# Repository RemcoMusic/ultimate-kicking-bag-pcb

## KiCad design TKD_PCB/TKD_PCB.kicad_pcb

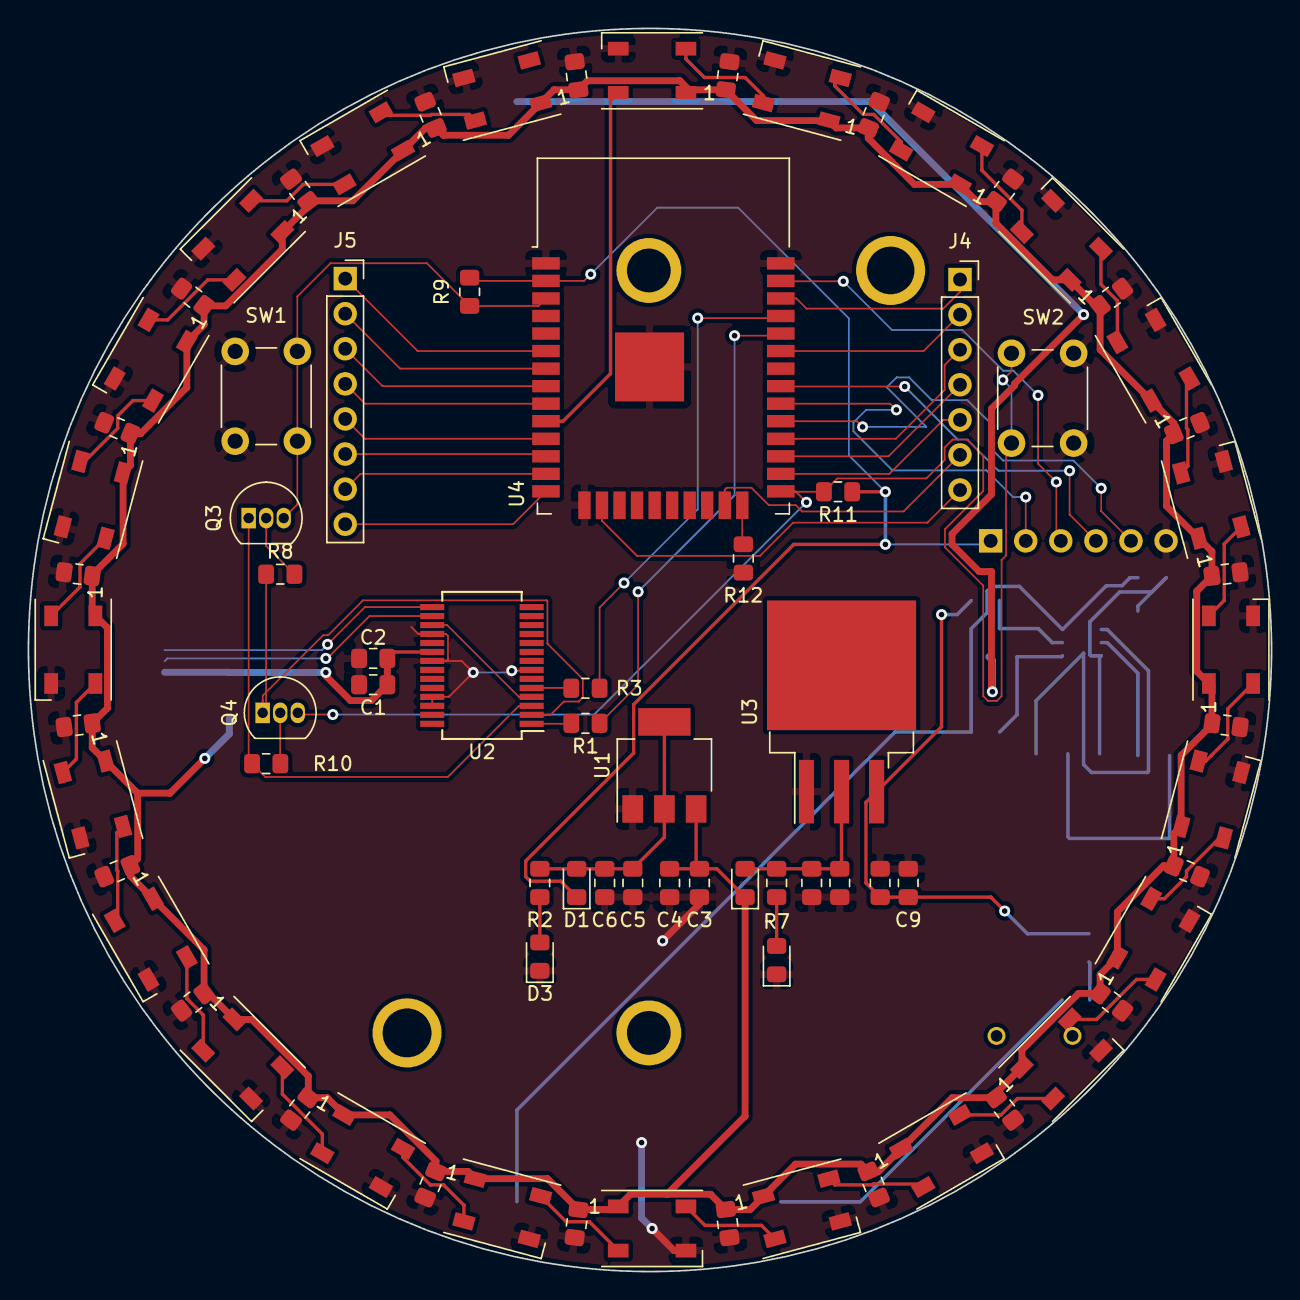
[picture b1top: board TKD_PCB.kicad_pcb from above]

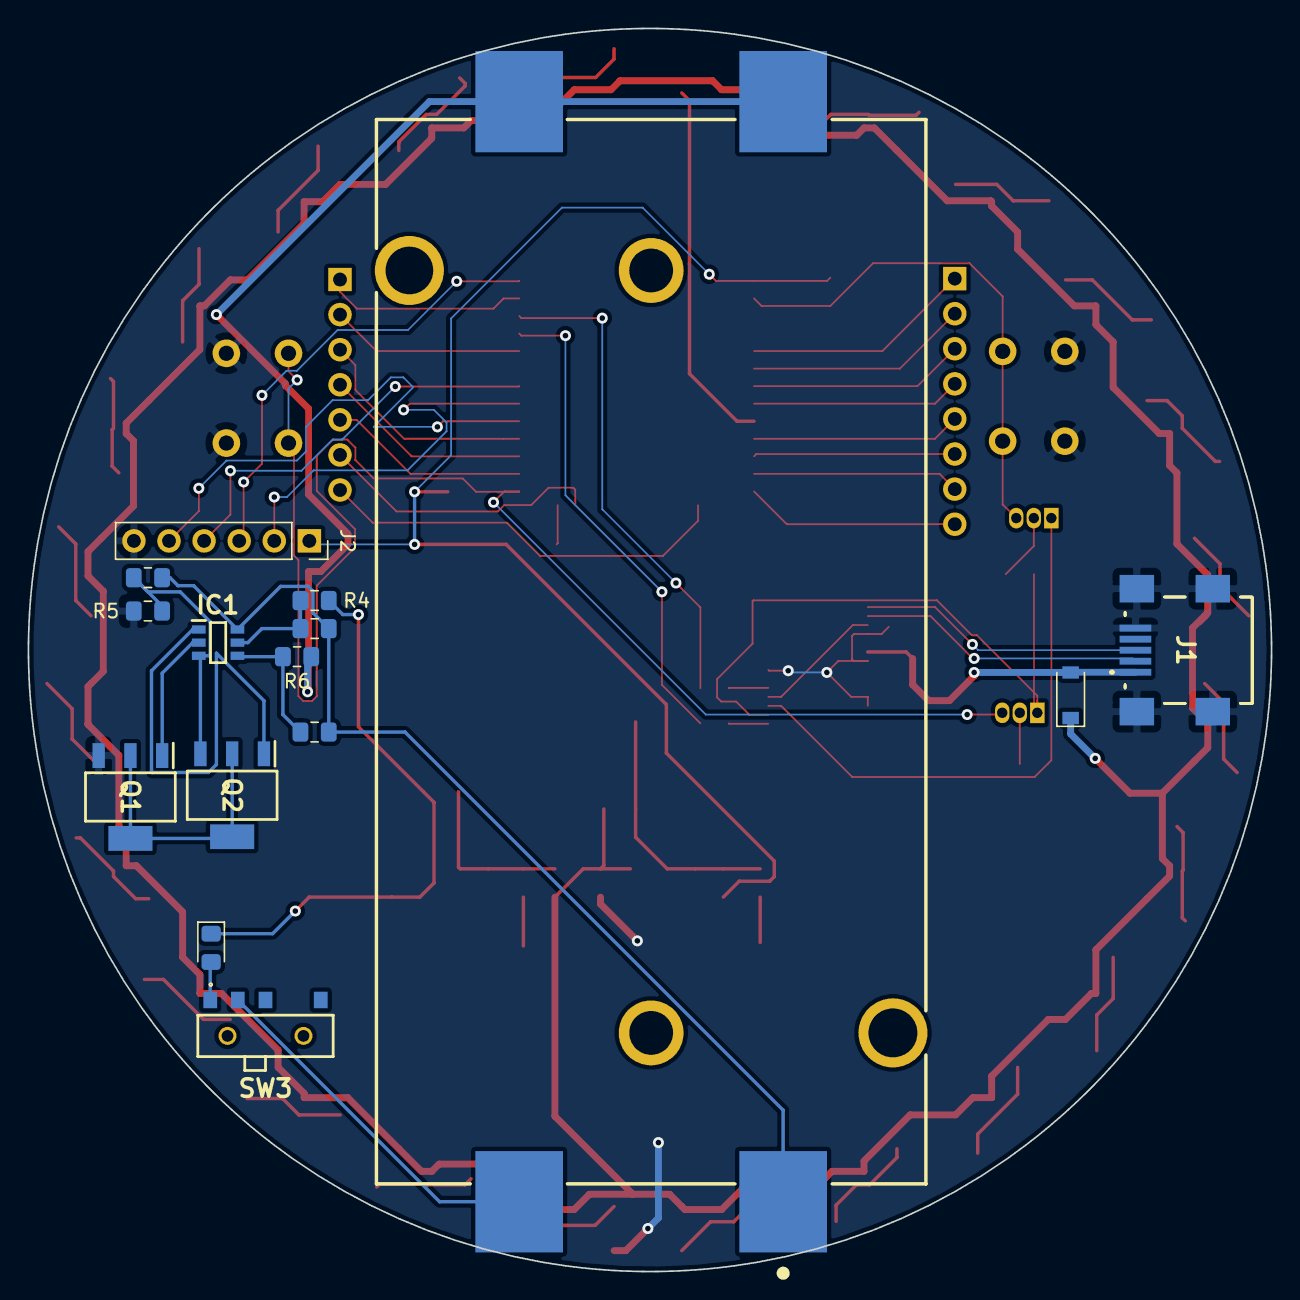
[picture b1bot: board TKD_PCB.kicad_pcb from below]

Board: 2 copper layers, 90.0 x 90.0 mm, 96 parts (15 on the bottom side), 76 nets.

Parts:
C1, C4, C5, C7, C9, C10, C12, C13, C14, C15, C16, C17, C18, C19, C20, C21, C22, C23, C24, C25, C26, C27, C28, C29, C30, C31, C32, C33, C34, C35, C36, C37: 100nF; C_0805_2012Metric_Pad1.15x1.40mm_HandSolder
C2, C3, C6, C8, C11: 10uF; C_0805_2012Metric_Pad1.15x1.40mm_HandSolder
D1, D4, D6: D; D_0805_2012Metric_Pad1.15x1.40mm_HandSolder
D2: D; D_SOD-123
D3, D5: LED; D_0805_2012Metric_Pad1.15x1.40mm_HandSolder
D7, D8, D9, D10, D11, D12, D13, D14, D15, D16, D17, D18, D19, D20, D21, D22, D23, D24, D25, D26, D27, D28, D29, D30: WS2812B; LED_WS2812B_PLCC4_5.0x5.0mm_P3.2mm
IC1: R5460N233AF-TR-FE; SOT95P280X140-6N
J1: USB2066-05-RBHM-15-STB-00-00-A; USB206605RBHM15STB0000A
J2: Conn_01x06; PinSocket_1x06_P2.54mm_Vertical
J4: Conn_01x07; PinSocket_1x07_P2.54mm_Vertical
J5: Conn_01x08; PinSocket_1x08_P2.54mm_Vertical
Q1, Q2: ZXMN6A09GQTA; SOT230P700X165-4N
Q3, Q4: S8050; TO-92_Inline
R1, R3: 22R; R_0805_2012Metric_Pad1.15x1.40mm_HandSolder
R2, R5, R7: 1k; R_0805_2012Metric_Pad1.15x1.40mm_HandSolder
R4, R6: 330R; R_0805_2012Metric_Pad1.15x1.40mm_HandSolder
R8, R10: 12k; R_0805_2012Metric_Pad1.15x1.40mm_HandSolder
R9, R11: 10k; R_0805_2012Metric_Pad1.15x1.40mm_HandSolder
R12: 5k; R_0805_2012Metric_Pad1.15x1.40mm_HandSolder
SW1, SW2: SW_Push; SW_PUSH_6mm
SW3: SW_SPDT; AYZ0103AGRLC
U1: AMS1117-3.3; SOT-223-3_TabPin2
U2: FT232RL; SSOP-28_5.3x10.2mm_P0.65mm
U3: LM1085-5.0; TO-263-3_TabPin4
U4: ESP32-WROOM-32D; ESP32-WROOM-32
U5: 1048

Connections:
+3V3: D1.1, J2.1, R9.1, R11.1, U4.2
+5V: C3.1, C4.2, C14.1, C15.1, C16.1, C17.1, C18.1, C19.1, C20.1, C21.1, C22.1, C23.1, C24.1, C25.1, C26.1, C27.1, C28.1, C29.1, C30.1, C31.1, C32.1, C33.1, C34.1, C35.1, C36.1, C37.1, D2.1, D4.1, D7.1, D8.1, D9.1, D10.1, D11.1, D12.1, D13.1, D14.1, D15.1, D16.1, D17.1, D18.1, D19.1, D20.1, D21.1, D22.1, D23.1, D24.1, D25.1, D26.1, D27.1, D28.1, D29.1, D30.1, U1.3
+BATT: C8.1, C9.2, D6.1, R4.1, U3.3
/EN: Q3.3, R9.2, SW1.1, U4.3
/Fastled_Pin: D7.4, U4.10
/GPIO0: Q4.3, R11.2, SW2.1, U4.25
/GPIO2: R12.2, U4.24
/GPIO4: J4.5, U4.26
/GPIO15: J4.6, U4.23
/GPIO16: J4.4, U4.27
/GPIO17: J4.3, U4.28
/GPIO21: J4.2, U4.33
/GPIO22: J4.1, U4.36
/GPIO26: J5.5, U4.11
/GPIO27: J5.6, U4.12
/GPIO32: J5.3, U4.8
/GPIO33: J5.4, U4.9
/GPIO34: J5.1, U4.6
/GPIO35: J5.2, U4.7
/HSPIMISO: J5.8, U4.14
/HSPIMOSI: J4.7, U4.16
/HSPISCLK: J5.7, U4.13
/RXD0: R1.1, U4.34
/TXD0: R3.1, U4.35
/USB_5V: C1.1, C2.1, D2.2, J1.1, U2.20
/VSPICLK: J2.2, U4.30
/VSPICS: J2.5, U4.29
/VSPI_SDI: J2.4, U4.31
/VSPI_SDO: J2.3, U4.37
Batt_1_+: R6.1, U5.2, U5.3
Batt_1_GND: C7.1, C12.1, C13.2, IC1.6, U5.1
Batt_2_+: SW3.2, U5.4
GND: C1.2, C2.2, C3.2, C4.1, C5.2, C6.2, C8.2, C9.1, C10.2, C11.2, C14.2, C15.2, C16.2, C17.2, C18.2, C19.2, C20.2, C21.2, C22.2, C23.2, C24.2, C25.2, C26.2, C27.2, C28.2, C29.2, C30.2, C31.2, C32.2, C33.2, C34.2, C35.2, C36.2, C37.2, D3.1, D5.1, D7.3, D8.3, D9.3, D10.3, D11.3, D12.3, D13.3, D14.3, D15.3, D16.3, D17.3, D18.3, D19.3, D20.3, D21.3, D22.3, D23.3, D24.3, D25.3, D26.3, D27.3, D28.3, D29.3, D30.3, J1.5, J1.MP1, J1.MP2, J1.MP3, J1.MP4, J2.6, Q1.3, R5.2, R12.1, SW1.2, SW2.2, U1.1, U2.7, U2.18, U2.21, U2.25, U2.26, U3.1, U4.1, U4.15, U4.38, U4.39
unnamed: C5.1, C6.1, D1.2, R2.1, U1.2
unnamed: C7.2, IC1.5, R4.2
unnamed: C10.1, C11.1, D4.2, R7.1, U3.2
unnamed: C12.2, IC1.3, Q2.3, R5.1
unnamed: C13.1, IC1.4, R6.2
unnamed: D3.2, R2.2
unnamed: D5.2, R7.2
unnamed: D6.2, SW3.1
unnamed: D7.2, D8.4
unnamed: D8.2, D9.4
unnamed: D10.2, D11.4
unnamed: D9.2, D10.4
unnamed: D11.2, D12.4
unnamed: D12.2, D13.4
unnamed: D13.2, D14.4
unnamed: D14.2, D15.4
unnamed: D15.2, D16.4
unnamed: D16.2, D17.4
unnamed: D17.2, D18.4
unnamed: D18.2, D19.4
unnamed: D19.2, D20.4
unnamed: D20.2, D21.4
unnamed: D21.2, D22.4
unnamed: D22.2, D23.4
unnamed: D23.2, D24.4
unnamed: D24.2, D25.4
unnamed: D25.2, D26.4
unnamed: D26.2, D27.4
unnamed: D27.2, D28.4
unnamed: D28.2, D29.4
unnamed: D29.2, D30.4
unnamed: IC1.1, Q2.1
unnamed: IC1.2, Q1.1
unnamed: J1.2, U2.16
unnamed: J1.3, U2.15
unnamed: Q1.2, Q1.4, Q2.2, Q2.4
unnamed: Q3.1, R10.1, U2.3
unnamed: Q3.2, R8.2
unnamed: Q4.1, R8.1, U2.2
unnamed: Q4.2, R10.2
unnamed: R1.2, U2.1
unnamed: R3.2, U2.5
unnamed: U2.4, U2.17

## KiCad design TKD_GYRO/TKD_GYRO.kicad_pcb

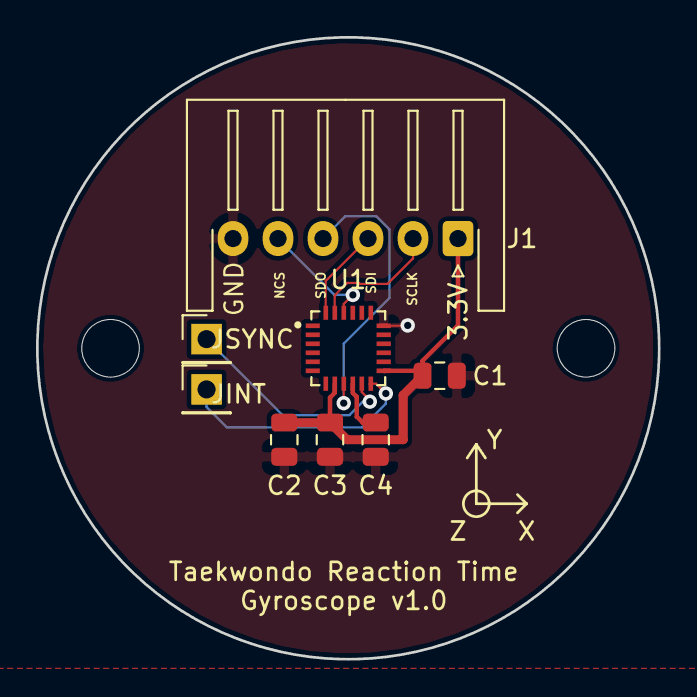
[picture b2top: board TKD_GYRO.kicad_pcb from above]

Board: 2 copper layers, 34.5 x 34.5 mm, 10 parts (0 on the bottom side), 9 nets.

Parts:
C1: 10nF; C_0805_2012Metric
C2: 2.2uF; C_0805_2012Metric
C3: 0.1uF; C_0805_2012Metric
C4: 0.47uF; C_0805_2012Metric
H1, H2: MountingHole; MountingHole_3.2mm_M3
J1: Conn_01x06; JST_XH_S6B-XH-A-1_1x06_P2.50mm_Horizontal
JINT: Conn_01x01; PinHeader_1x01_P2.54mm_Vertical
JSYNC: Conn_01x01; PinHeader_1x01_P2.54mm_Vertical
U1: ICM-20689; QFN50P400X400X95-24N

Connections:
+3V3: C1.1, C2.1, C3.1, J1.1, U1.8, U1.13
AD0-SDO: J1.4, U1.9
FSYNC: JSYNC.1, U1.11
GND: C1.2, C2.2, C3.2, C4.1, J1.6, U1.18
INT: JINT.1, U1.12
NCS: J1.5, U1.22
unnamed: C4.2, U1.10
SCL-SCLK: J1.2, U1.23
SDA-SDI: J1.3, U1.24

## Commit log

2020-10-25 First commit of PCB schematic design
2021-02-11 Second revision with battery protection circuit attempt
2021-02-12 Auto programming circuit added
2021-06-21 Begin of the final assembly
2021-06-28 did Remco's homework
2021-06-28 some more routing
2021-06-29 made PCB smaller
2021-07-19 Gyro PCB created and finished ready to order
2021-07-30 Final check before ordering
